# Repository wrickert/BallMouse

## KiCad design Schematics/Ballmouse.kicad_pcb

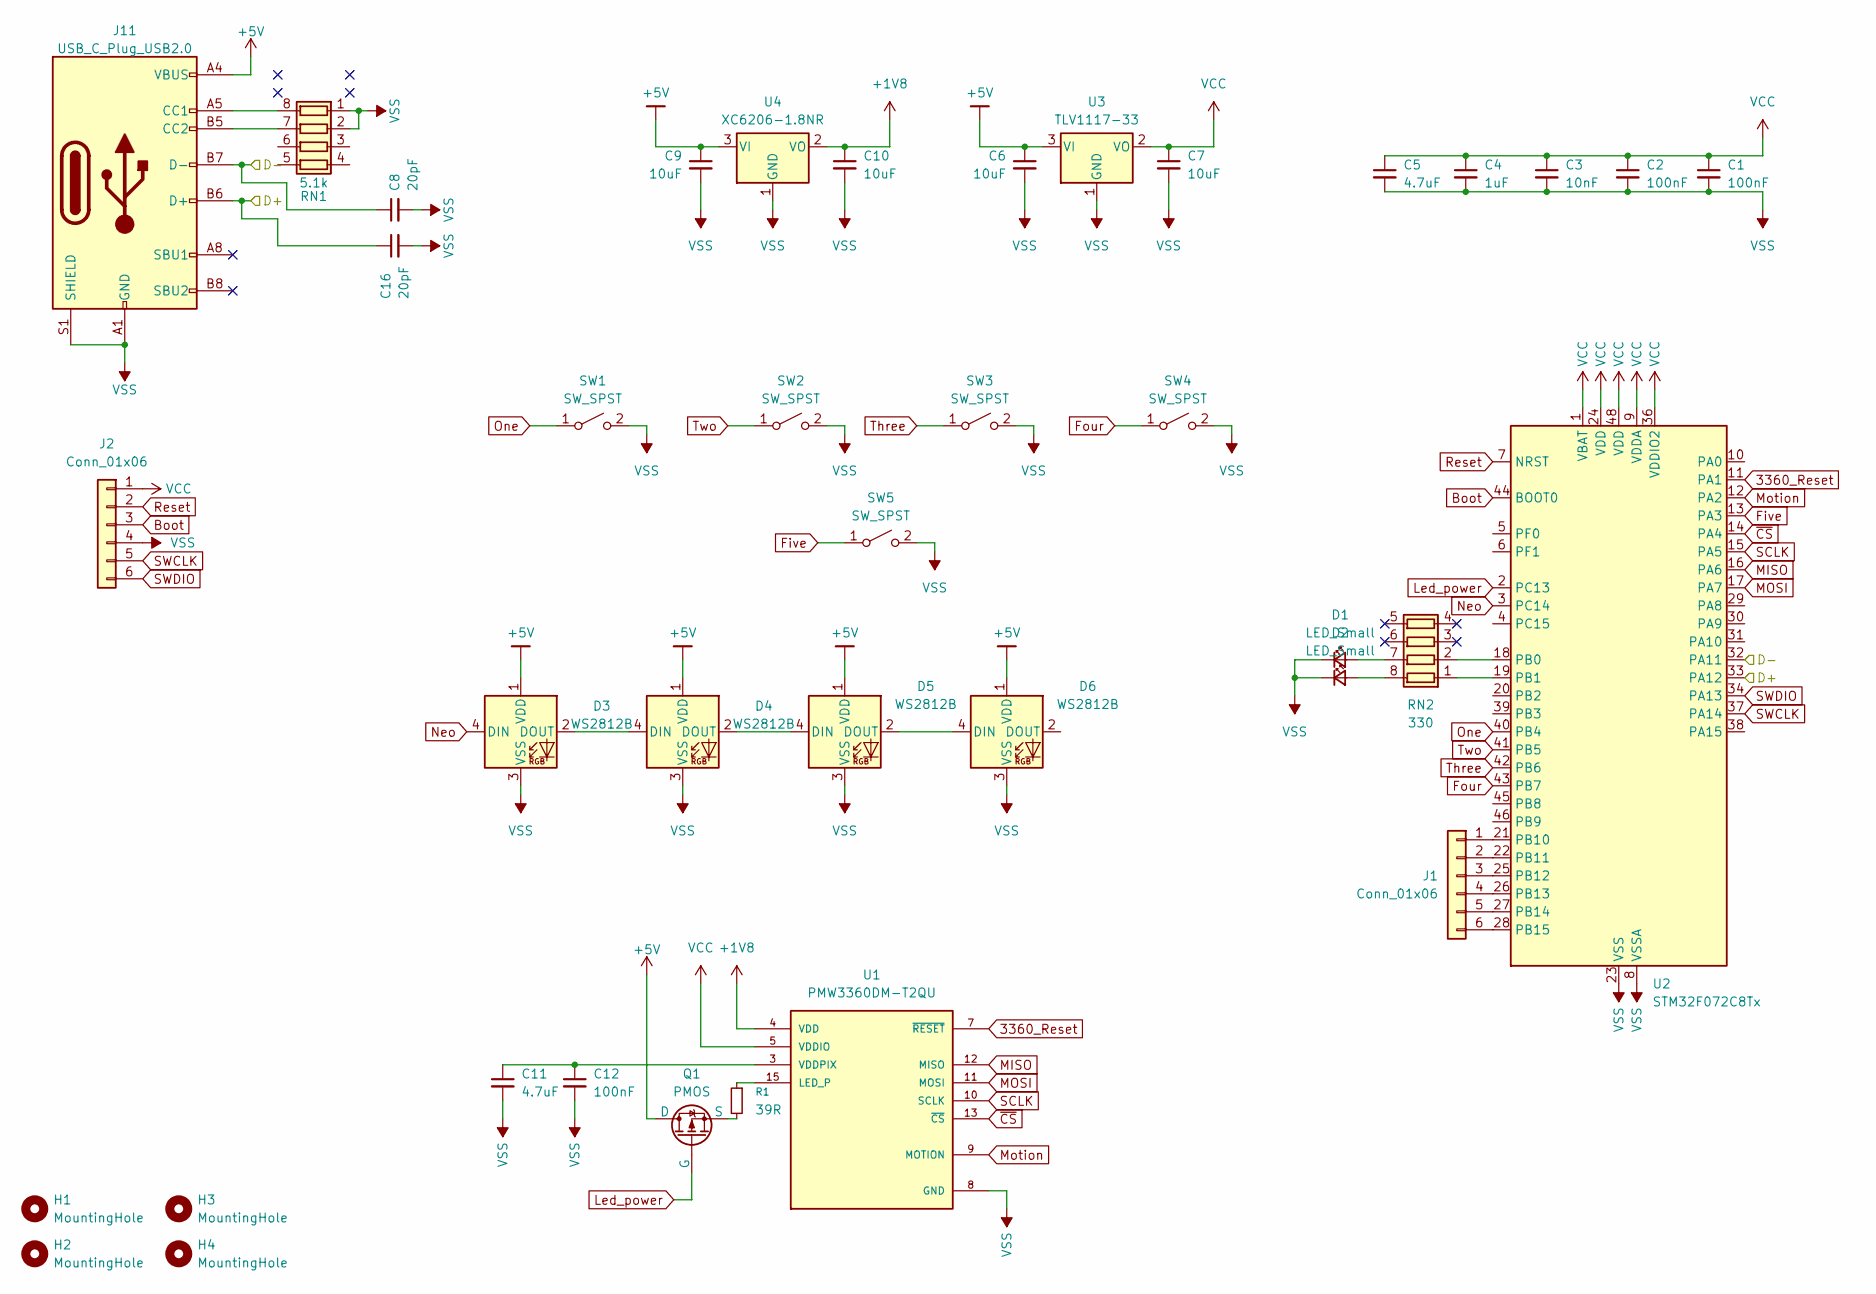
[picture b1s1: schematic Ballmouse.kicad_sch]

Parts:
C1, C2, C12: 100nF; C_0805_2012Metric
C3: 10nF; C_0805_2012Metric
C4: 1uF; C_0805_2012Metric
C5, C11: 4.7uF; C_0805_2012Metric
C6, C7, C9, C10: 10uF; C_0805_2012Metric
C8, C16: 20pF; C_0603_1608Metric
D1, D2: LED_Small; LED_0805_2012Metric
D3, D4, D5, D6: WS2812B; SK6812-E_FaceUp
H1, H2, H3, H4: MountingHole; M3ThreadedStandoff
J1: Conn_01x06; PinHeader_1x06_P1.27mm_Vertical
J2: Conn_01x06; PinHeader_1x06_P2.54mm_Vertical
J11: USB_C_Plug_USB2.0; USB_C_Receptical-Jing
Q1: PMOS; SOT-23
R1: 39R; R_0805_2012Metric
RN1: 5.1k; R_Array_Convex_4x0603
RN2: 330; R_Array_Convex_4x0603
SW1, SW2, SW3, SW4, SW5: SW_SPST; TS3315A
U1: PMW3360DM-T2QU; PMW3360; MANUFACTURER_PART_NUMBER PMW3360DM-T2QU
U2: STM32F072C8Tx; LQFP-48_7x7mm_P0.5mm
U3: TLV1117-33; SOT-223-3_TabPin2
U4: XC6206-1.8NR; SOT-23

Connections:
3360_Reset: U1.7 (~RESET), U2.11 (PA1)
+1V8: C10.1, U1.4 (VDD), U4.2 (VO)
+5V: C6.1, C9.1, D3.1 (VDD), D4.1 (VDD), D5.1 (VDD), D6.1 (VDD), J11.A4 (VBUS), J11.A9 (VBUS), J11.B4 (VBUS), J11.B9 (VBUS), Q1.3 (D), U3.3 (VI), U4.3 (VI)
/D+: C16.1, J11.A6 (D+), J11.B6 (D+), U2.33 (PA12)
/D-: C8.1, J11.A7 (D-), J11.B7 (D-), U2.32 (PA11)
Boot: J2.3, U2.44 (BOOT0)
Five: SW5.1 (A), U2.13 (PA3)
Four: SW4.1 (A), U2.43 (PB7)
Led_power: Q1.1 (G), U2.2 (PC13)
MISO: U1.12 (MISO), U2.16 (PA6)
MOSI: U1.11 (MOSI), U2.17 (PA7)
Motion: U1.9 (MOTION), U2.12 (PA2)
Neo: D3.4 (DIN), U2.3 (PC14)
unnamed: D1.2 (A), RN2.7 (R2.2)
unnamed: D2.2 (A), RN2.8 (R1.2)
unnamed: D3.2 (DOUT), D4.4 (DIN)
unnamed: D4.2 (DOUT), D5.4 (DIN)
unnamed: D5.2 (DOUT), D6.4 (DIN)
unnamed: J1.1, U2.21 (PB10)
unnamed: J1.2, U2.22 (PB11)
unnamed: J1.3, U2.25 (PB12)
unnamed: J1.4, U2.26 (PB13)
unnamed: J1.5, U2.27 (PB14)
unnamed: J1.6, U2.28 (PB15)
unnamed: J11.A5 (CC1), RN1.8 (R1.2)
unnamed: J11.B5 (CC2), RN1.7 (R2.2)
unnamed: Q1.2 (S), R1.2
unnamed: RN2.1 (R1.1), U2.19 (PB1)
unnamed: RN2.2 (R2.1), U2.18 (PB0)
unnamed: R1.1, U1.15 (LED_P)
unnamed: C11.1, C12.1, U1.3 (VDDPIX)
One: SW1.1 (A), U2.40 (PB4)
Reset: J2.2, U2.7 (NRST)
SCLK: U1.10 (SCLK), U2.15 (PA5)
SWCLK: J2.5, U2.37 (PA14)
SWDIO: J2.6, U2.34 (PA13)
Three: SW3.1 (A), U2.42 (PB6)
Two: SW2.1 (A), U2.41 (PB5)
VCC: C1.1, C2.1, C3.1, C4.1, C5.1, C7.1, J2.1, U1.5 (VDDIO), U2.1 (VBAT), U2.9 (VDDA), U2.24 (VDD), U2.36 (VDDIO2), U2.48 (VDD), U3.2 (VO)
VSS: C1.2, C2.2, C3.2, C4.2, C5.2, C6.2, C7.2, C8.2, C9.2, C10.2, C11.2, C12.2, C16.2, D1.1 (K), D2.1 (K), D3.3 (VSS), D4.3 (VSS), D5.3 (VSS), D6.3 (VSS), J2.4, J11.A1 (GND), J11.A12 (GND), J11.B1 (GND), J11.B12 (GND), J11.S1 (SHIELD), RN1.1 (R1.1), RN1.2 (R2.1), SW1.2 (B), SW2.2 (B), SW3.2 (B), SW4.2 (B), SW5.2 (B), U1.8 (GND), U2.8 (VSSA), U2.23 (VSS), U2.35 (VSS), U2.47 (VSS), U3.1 (GND), U4.1 (GND)
~CS: U1.13 (~CS), U2.14 (PA4)

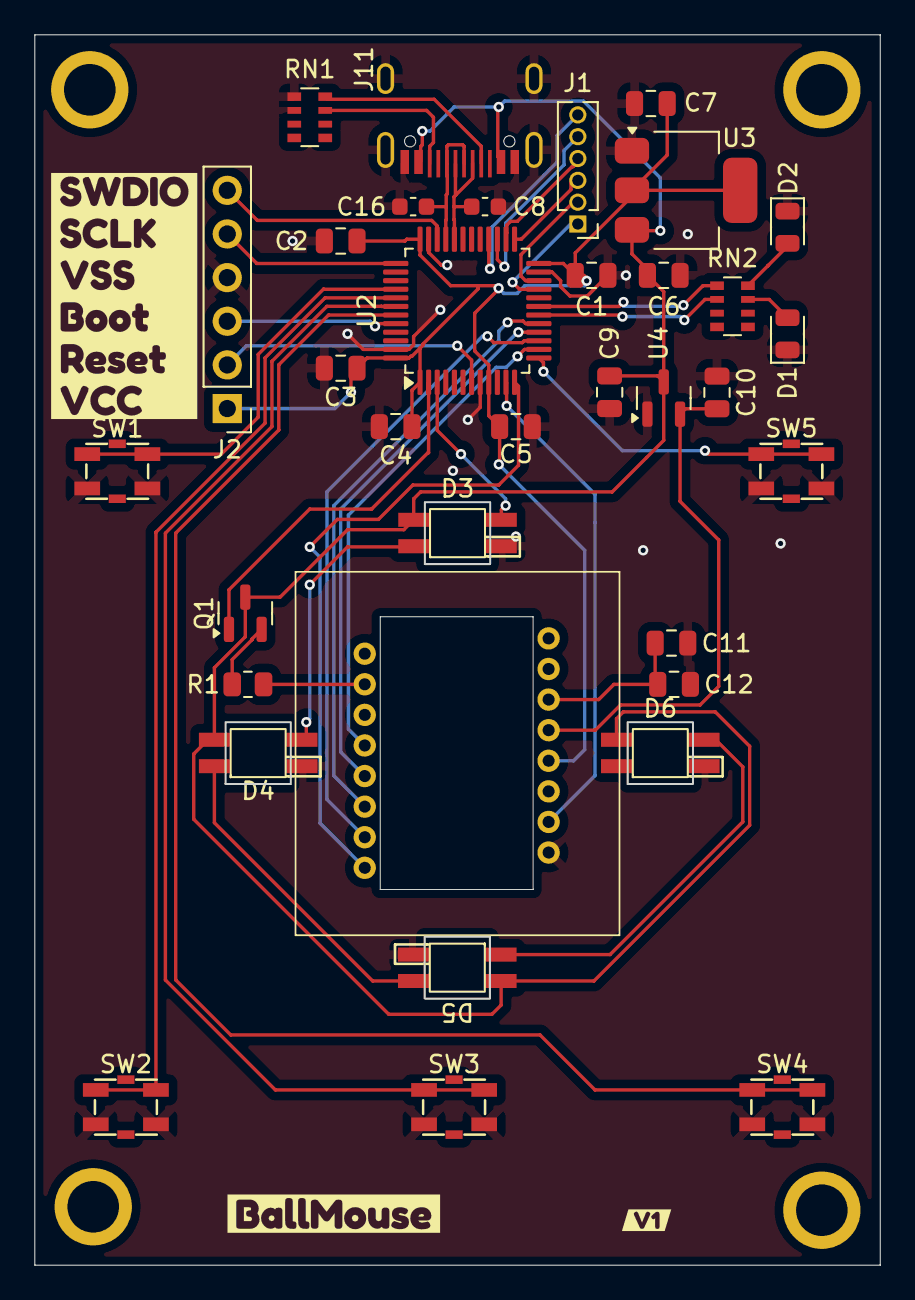
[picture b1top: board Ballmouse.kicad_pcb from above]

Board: 2 copper layers, 49.1 x 71.5 mm, 42 parts (1 on the bottom side), 41 nets.

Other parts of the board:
kibuzzard-691E3A0F: G***; kibuzzard-691E3A0F
kibuzzard-691E3A1E: G***; kibuzzard-691E3A1E
kibuzzard-691E39CE: G***; kibuzzard-691E39CE

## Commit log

2025-11-17 Added files
2025-11-19 Unrouted:0. Should I add leds?
2025-11-20 Ready to order PCB
